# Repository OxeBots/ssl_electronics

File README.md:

# ssl_electronics
Oxebots electronics design for the RoboCup Soccer Small-Size League

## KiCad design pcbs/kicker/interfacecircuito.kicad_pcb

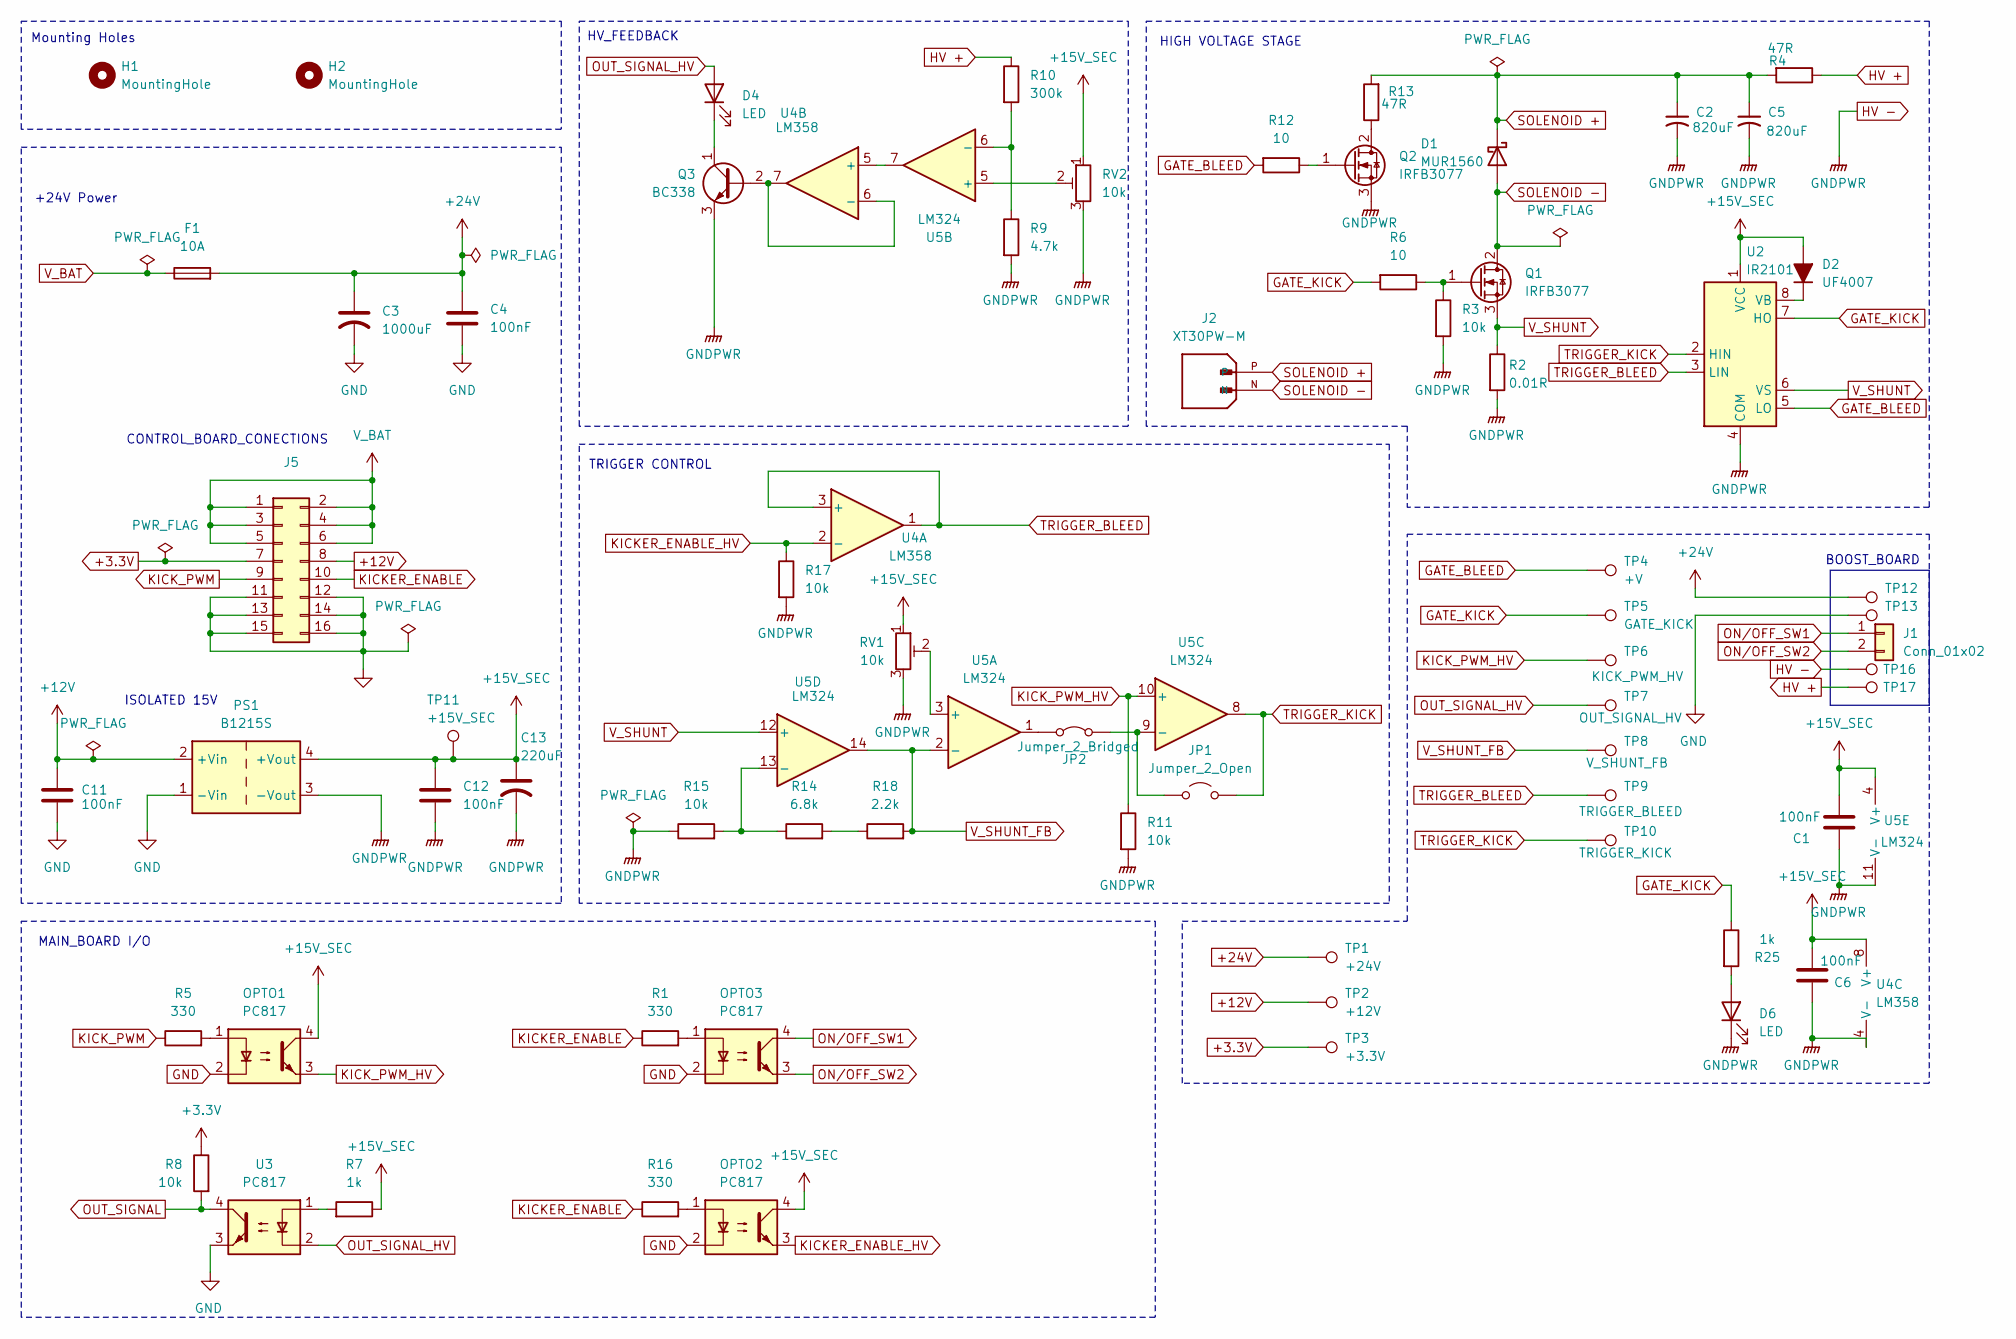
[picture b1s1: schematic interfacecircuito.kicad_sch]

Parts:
C1, C4, C6, C11, C12: 100nF; C_Disc_D5.0mm_W2.5mm_P2.50mm
C2, C5: 820uF; CP_Radial_D30.0mm_P10.00mm_SnapIn
C3: 1000uF; CP_Radial_D8.0mm_P5.00mm
C13: 220uF; CP_Radial_D8.0mm_P5.00mm
D1: MUR1560; TO-220-2_Vertical
D2: UF4007; D_DO-41_SOD81_P10.16mm_Horizontal
D4, D6: LED; LED_D5.0mm
F1: 10A; Fuse_Blade_ATO_directSolder
H1, H2: MountingHole; MountingHole_4.3mm_M4_Pad_Via
J1: Conn_01x02; JST_EH_B2B-EH-A_1x02_P2.50mm_Vertical
J2: XT30PW-M; AMASS_XT30PW-M; PARTREV 1.2
J5: Conn_02x08_Odd_Even; IDC-Header_2x08_P2.54mm_Vertical
JP1: Jumper_2_Open; SolderJumper-2_P1.3mm_Open_RoundedPad1.0x1.5mm
JP2: Jumper_2_Bridged; SolderJumper-2_P1.3mm_Bridged_RoundedPad1.0x1.5mm
OPTO1, OPTO2, OPTO3: PC817; DIP-4_W7.62mm
PS1: B1215S; DC-DC_Converter_BxxxxS_1W
Q1, Q2: IRFB3077; TO-220-3_Vertical
Q3: BC338; TO-92_Inline
R1, R5, R16: 330; R_Axial_DIN0207_L6.3mm_D2.5mm_P10.16mm_Horizontal
R2: 0.01R; R_Axial_DIN0516_L15.5mm_D5.0mm_P20.32mm_Horizontal
R3, R8, R11, R15, R17: 10k; R_Axial_DIN0207_L6.3mm_D2.5mm_P10.16mm_Horizontal
R4, R13: 47R; R_Axial_Power_L25.0mm_W9.0mm_P30.48mm
R6, R12: 10; R_Axial_DIN0207_L6.3mm_D2.5mm_P10.16mm_Horizontal
R7, R25: 1k; R_Axial_DIN0207_L6.3mm_D2.5mm_P10.16mm_Horizontal
R9: 4.7k; R_Axial_DIN0207_L6.3mm_D2.5mm_P10.16mm_Horizontal
R10: 300k; R_Axial_DIN0411_L9.9mm_D3.6mm_P15.24mm_Horizontal
R14: 6.8k; R_Axial_DIN0207_L6.3mm_D2.5mm_P10.16mm_Horizontal
R18: 2.2k; R_Axial_DIN0207_L6.3mm_D2.5mm_P10.16mm_Horizontal
RV1, RV2: 10k; Potentiometer_Bourns_3296W_Vertical
TP1: +24V; TestPoint_Pad_D1.5mm
TP2: +12V; TestPoint_Pad_D1.5mm
TP3: +3.3V; TestPoint_Pad_D1.5mm
TP4: +V; TestPoint_Pad_D1.5mm
TP5: GATE_KICK; TestPoint_Pad_D1.5mm
TP6: KICK_PWM_HV; TestPoint_Pad_D1.5mm
TP7: OUT_SIGNAL_HV; TestPoint_Pad_D1.5mm
TP8: V_SHUNT_FB; TestPoint_Pad_D1.5mm
TP9: TRIGGER_BLEED; TestPoint_Pad_D1.5mm
TP10: TRIGGER_KICK; TestPoint_Pad_D1.5mm
TP11: +15V_SEC; TestPoint_Pad_D1.5mm
TP12: V+; TestPoint_Plated_Hole_D2.0mm
TP13: GND; TestPoint_Plated_Hole_D2.0mm
TP16: HV-; TestPoint_Plated_Hole_D2.0mm
TP17: HV+; TestPoint_Plated_Hole_D2.0mm
U2: IR2101; SOIC-8_3.9x4.9mm_P1.27mm
U3: PC817; DIP-4_W7.62mm
U4: LM358; SOIC-8_3.9x4.9mm_P1.27mm
U5: LM324; SOIC-14_3.9x8.7mm_P1.27mm

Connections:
+3.3V: J5.7, R8.1, TP3.1 (1_1)
+12V: C11.1, J5.8, PS1.2 (+Vin), TP2.1 (1_1)
+15V_SEC: C1.1, C6.1, C12.1, C13.1, D2.2 (A), OPTO1.4, OPTO2.4, PS1.4 (+Vout), R7.1, RV1.1, RV2.1, TP11.1 (1_1), U2.1 (VCC), U4.8 (V+), U5.4 (V+)
+24V: C3.1, C4.1, F1.2, TP1.1 (1_1), TP12.1 (1_1)
GATE_BLEED: R12.2, TP4.1 (1_1), U2.5 (LO)
GATE_KICK: R6.2, R25.1, TP5.1 (1_1), U2.7 (HO)
GND: C3.2, C4.2, C11.2, J5.11, J5.12, J5.13, J5.14, J5.15, J5.16, OPTO1.2, OPTO2.2, OPTO3.2, PS1.1 (-Vin), TP13.1 (1_1), U3.3
HV +: R4.1, R10.1, TP17.1 (1_1)
HV -: C1.2, C2.2, C5.2, C6.2, C12.2, C13.2, D6.1 (K), PS1.3 (-Vout), Q2.3 (S), Q3.3 (E), R2.2, R3.2, R9.2, R11.2, R15.1, R17.2, RV1.3, RV2.3, TP16.1 (1_1), U2.4 (COM), U4.4 (V-), U5.11 (V-)
KICKER_ENABLE: J5.10, R1.1, R16.1
KICKER_ENABLE_HV: OPTO2.3, R17.1, U4.2 (-)
KICK_PWM: J5.9, R5.1
KICK_PWM_HV: OPTO1.3, R11.1, TP6.1 (1_1), U5.10 (+)
unnamed: D2.1 (K), U2.8 (VB)
unnamed: D4.1 (K), Q3.1 (C)
unnamed: D6.2 (A), R25.2
unnamed: JP1.1 (A), JP2.2 (B), U5.9 (-)
unnamed: JP2.1 (A), U5.1
unnamed: OPTO1.1, R5.2
unnamed: OPTO2.1, R16.2
unnamed: OPTO3.1, R1.2
unnamed: Q1.1 (G), R3.1, R6.1
unnamed: Q2.2 (D), R13.1
unnamed: Q2.1 (G), R12.1
unnamed: Q3.2 (B), U4.6 (-), U4.7
unnamed: R7.2, U3.1
unnamed: R14.2, R18.1
unnamed: U4.5 (+), U5.7
unnamed: RV1.2, U5.3 (+)
unnamed: RV2.2, U5.5 (+)
unnamed: R9.1, R10.2, U5.6 (-)
unnamed: R14.1, R15.2, U5.13 (-)
ON/OFF_SW1: J1.1, OPTO3.4
ON/OFF_SW2: J1.2, OPTO3.3
OUT_SIGNAL: R8.2, U3.4
OUT_SIGNAL_HV: D4.2 (A), TP7.1 (1_1), U3.2
SOLENOID +: C2.1, C5.1, D1.1 (K), J2.P, R4.2, R13.2
SOLENOID -: D1.2 (A), J2.N, Q1.2 (D)
TRIGGER_BLEED: TP9.1 (1_1), U2.3 (LIN), U4.1, U4.3 (+)
TRIGGER_KICK: JP1.2 (B), TP10.1 (1_1), U2.2 (HIN), U5.8
V_BAT: F1.1, J5.1, J5.2, J5.3, J5.4, J5.5, J5.6
V_SHUNT: Q1.3 (S), R2.1, U2.6 (VS), U5.12 (+)
V_SHUNT_FB: R18.2, TP8.1 (1_1), U5.2 (-), U5.14

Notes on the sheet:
CONTROL_BOARD_CONECTIONS
BOOST_BOARD
HIGH VOLTAGE STAGE
HV_FEEDBACK
TRIGGER CONTROL
MAIN_BOARD I/O
Mounting Holes
ISOLATED 15V
+24V Power

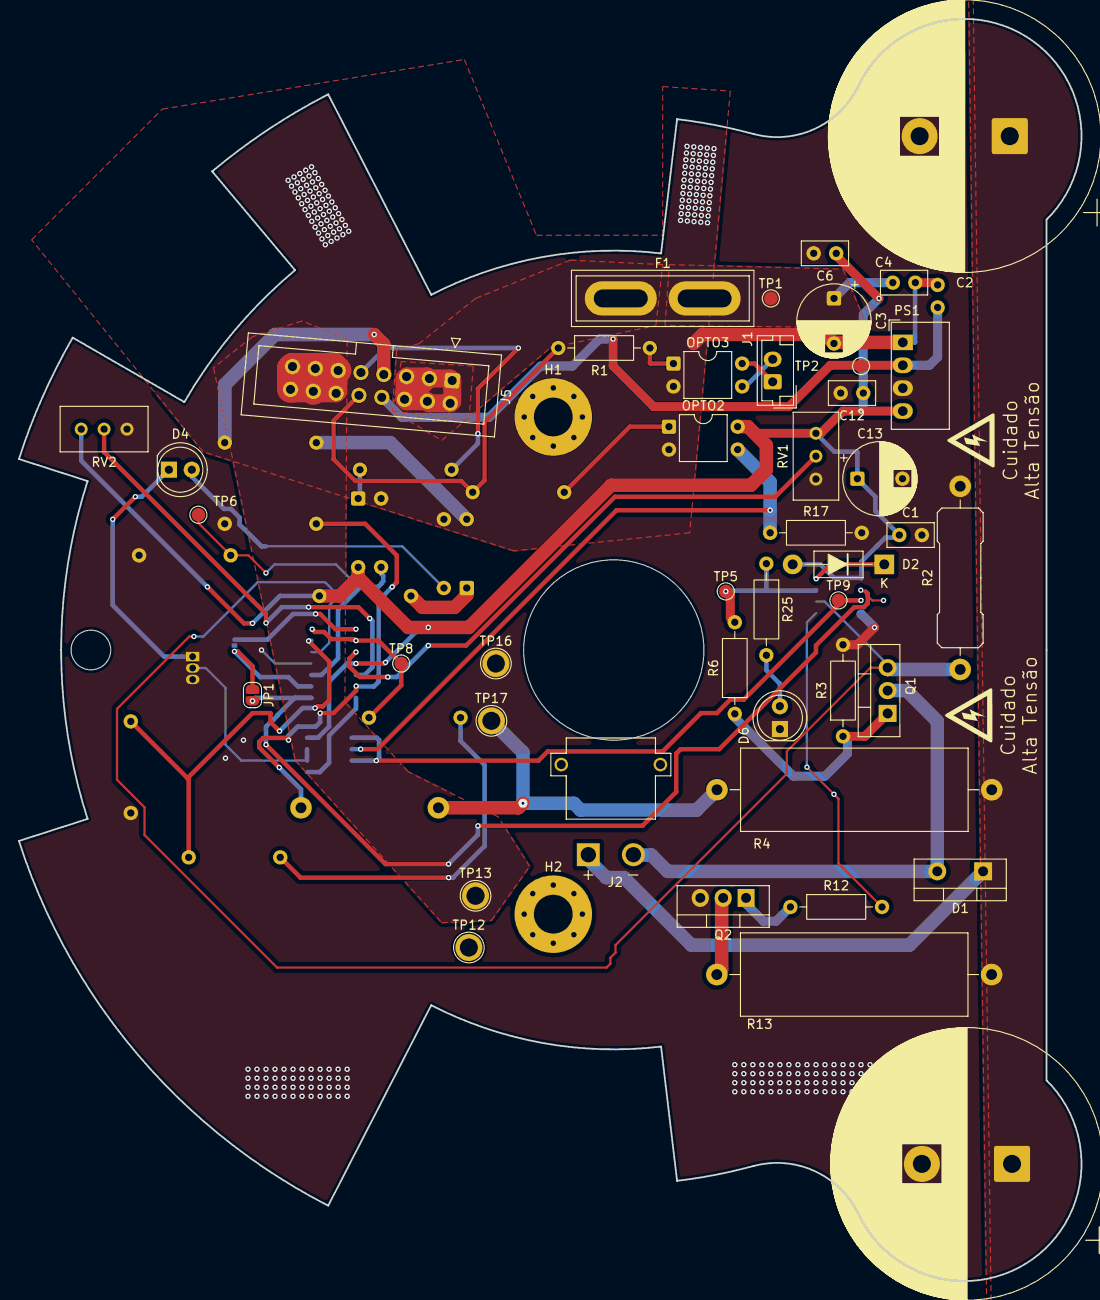
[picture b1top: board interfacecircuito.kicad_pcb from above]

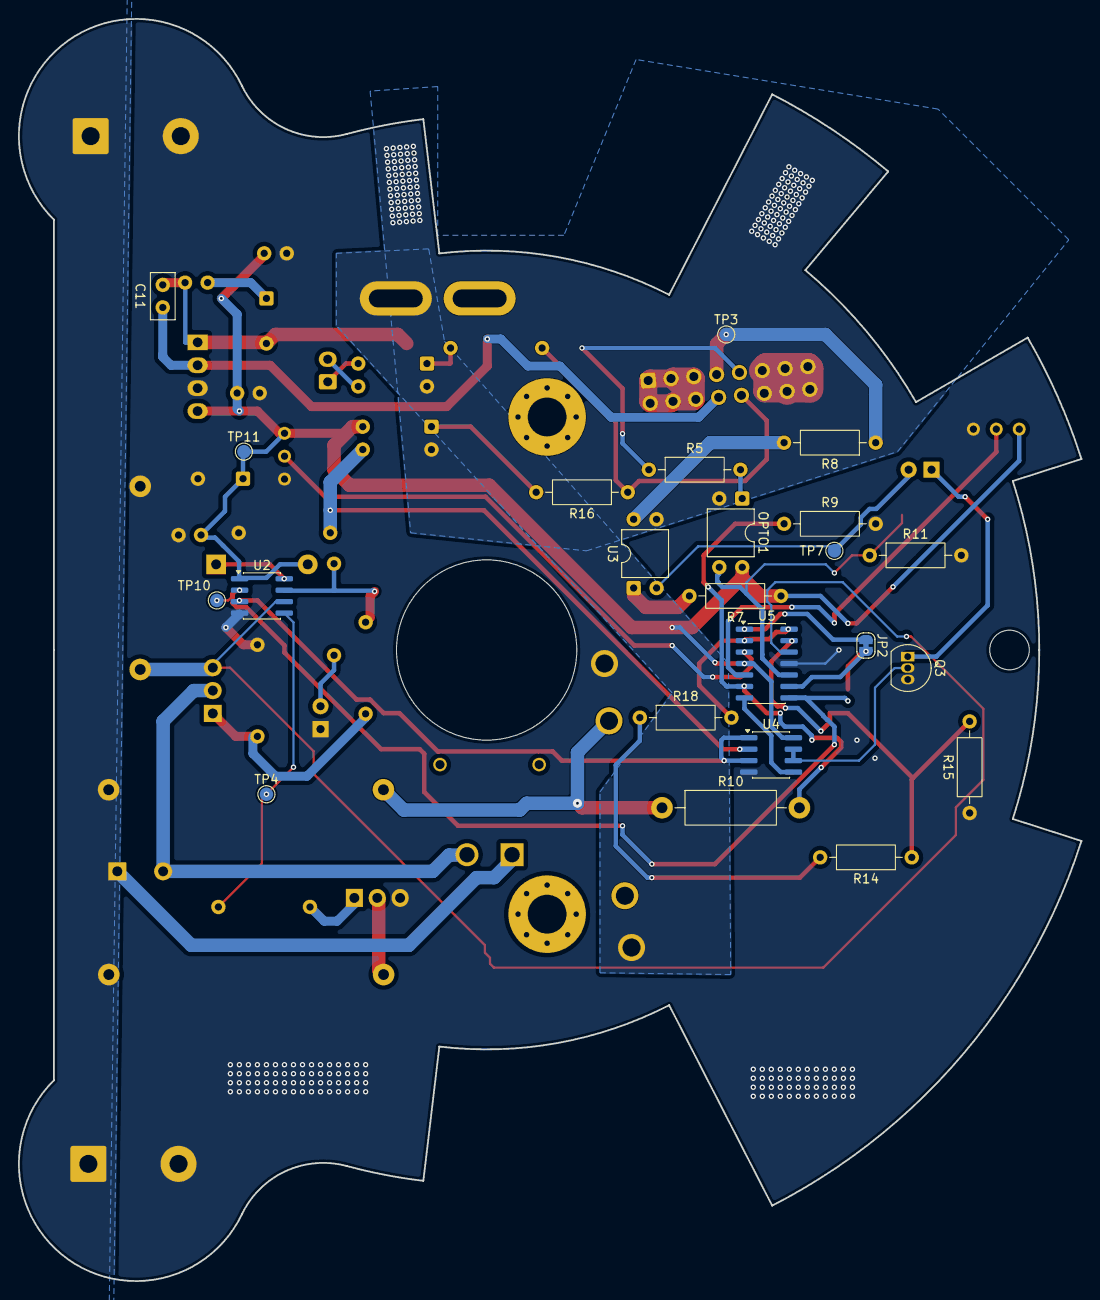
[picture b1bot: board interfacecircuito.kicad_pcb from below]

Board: 2 copper layers, 117.9 x 140.0 mm, 68 parts (23 on the bottom side), 43 nets.

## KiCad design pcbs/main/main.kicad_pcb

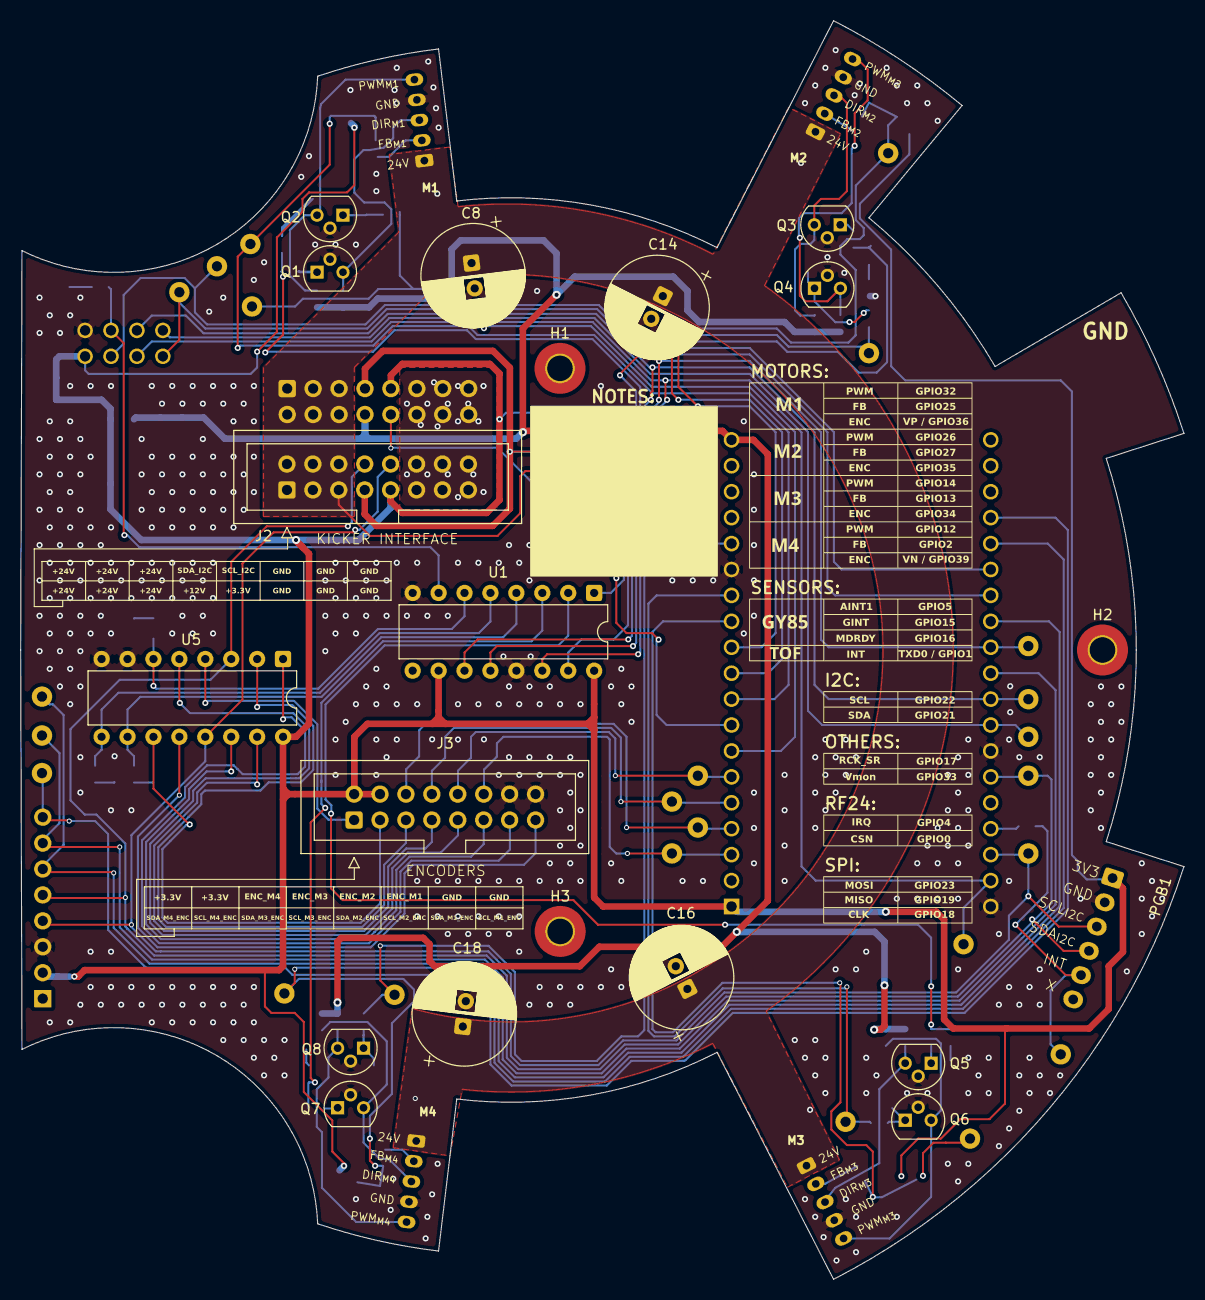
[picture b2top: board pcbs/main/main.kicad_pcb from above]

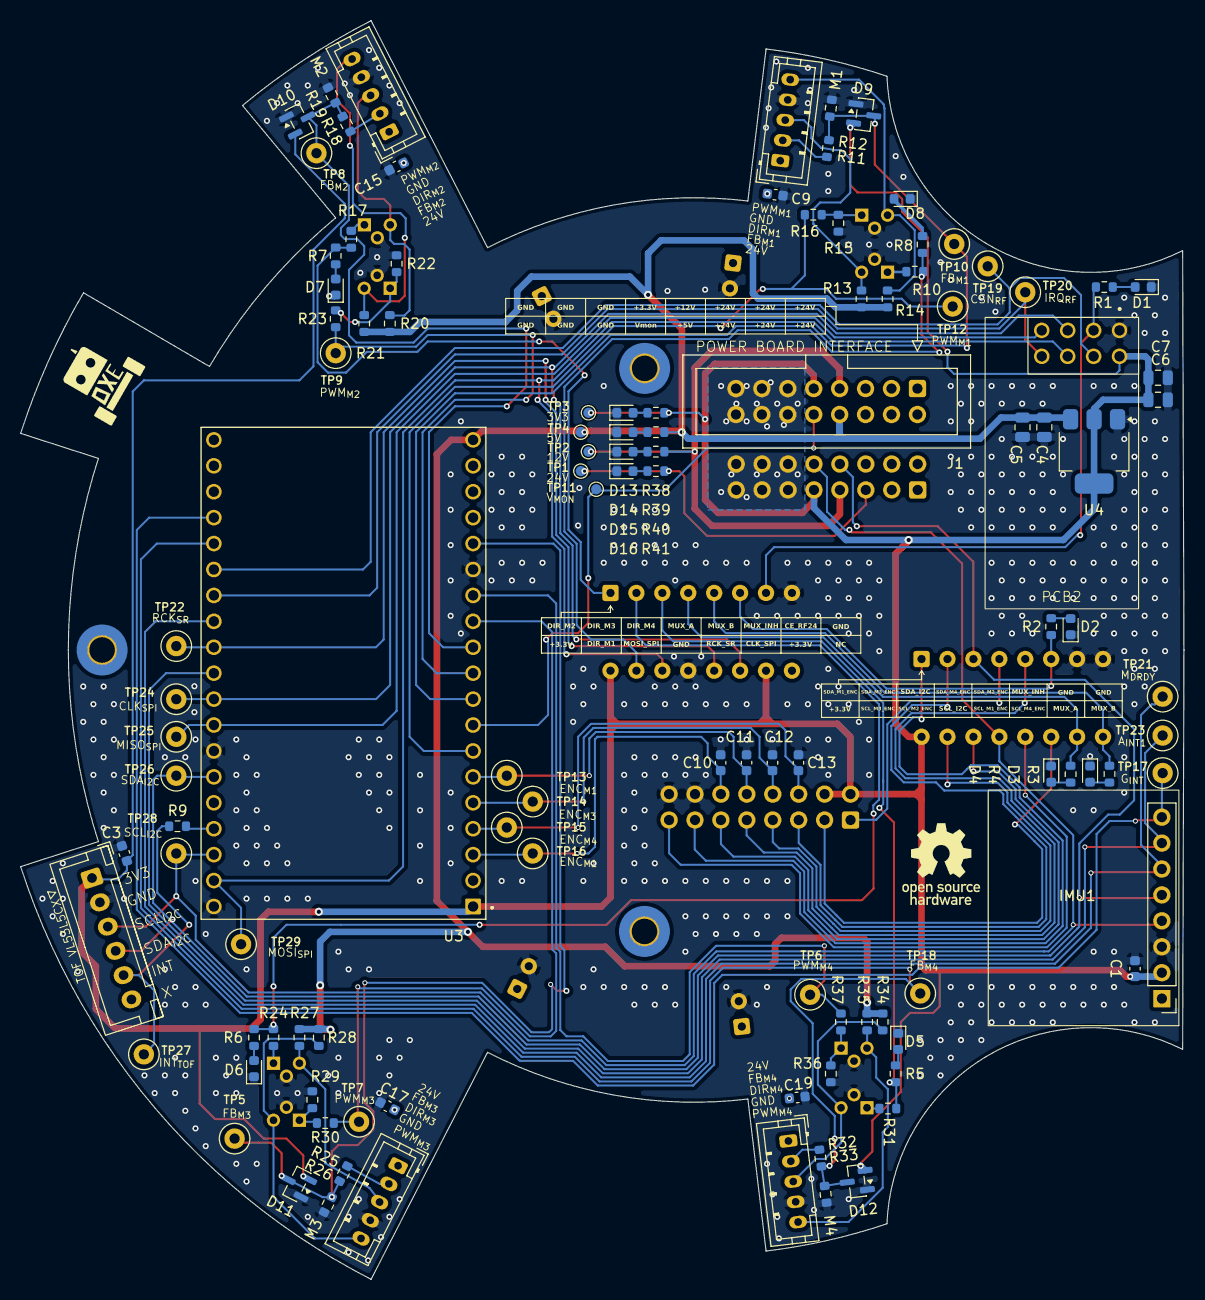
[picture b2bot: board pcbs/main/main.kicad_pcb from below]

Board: 2 copper layers, 114.0 x 123.3 mm, 129 parts (110 on the bottom side), 79 nets.

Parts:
C1, C3, C9, C10, C11, C12, C13, C15, C17, C19: 100 nF; C_0603_1608Metric
C4, C5, C6, C7: 10 uF; C_0805_2012Metric
C8, C14, C16, C18: 47uF; CP_Radial_D10.0mm_P2.50mm
D1, D2, D3, D4, D5, D6, D7, D8, D13, D14, D15, D16: LED; LED_0603_1608Metric
D9, D10, D11, D12: BAT54S; SOT-23
H1, H2, H3: MountingHole; MountingHole_2.5mm_Pad_TopBottom
IMU1: GY 85; GY-085
J1: PB_IDC_16_PIN; IDC-Header_2x08_P2.54mm_Vertical
J2: KICKER_IDC_16_PIN; IDC-Header_2x08_P2.54mm_Vertical
J3: ENC_IDC_16_PIN; IDC-Header_2x08_P2.54mm_Vertical
M1: FRONT_LEFT_MOTOR; HY-5_P2.00mm_Vertical
M2: BACK_LEFT_MOTOR; HY-5_P2.00mm_Vertical
M3: BACK_RIGHT_MOTOR; HY-5_P2.00mm_Vertical
M4: FRONT_RIGHT_MOTOR; HY-5_P2.00mm_Vertical
PCB1: VL53L5CX; JST_XH_B6B-XH-A_1x06_P2.50mm_Vertical
PCB2: NRF24L01
Q1, Q2, Q3, Q4, Q5, Q6, Q7, Q8: 2SC945; TO-92
R1, R2, R3, R4, R5, R6, R7, R8, R38, R39, R40, R41: 220; R_0603_1608Metric
R9, R10, R11, R13, R14, R16, R17, R18, R20, R21, R23, R24, R25, R27, R28, R30, R31, R32, R34, R35, R37: 10k; R_0603_1608Metric
R12, R19, R26, R33: 20k; R_0603_1608Metric
R15, R22, R29, R36: 47k; R_0603_1608Metric
TP1: 24V probe; TestPoint_Pad_D1.0mm
TP2: 12V probe; TestPoint_Pad_D1.0mm
TP3: 3.3V probe; TestPoint_Pad_D1.0mm
TP4: 5V probe; TestPoint_Pad_D1.0mm
TP5: M3_FB_Probe; TestPoint_Loop_D2.50mm_Drill1.0mm_LowProfile
TP6: M4_PWM_Probe; TestPoint_Loop_D2.50mm_Drill1.0mm_LowProfile
TP7: M3_PWM_Probe; TestPoint_Loop_D2.50mm_Drill1.0mm_LowProfile
TP8: M2_FB_Probe; TestPoint_Loop_D2.50mm_Drill1.0mm_LowProfile
TP9: M2_PWM_Probe; TestPoint_Loop_D2.50mm_Drill1.0mm_LowProfile
TP10: M1_FB_Probe; TestPoint_Loop_D2.50mm_Drill1.0mm_LowProfile
TP11: V_{mon} probe; TestPoint_Pad_D1.0mm
TP12: M1_PWM_Probe; TestPoint_Loop_D2.50mm_Drill1.0mm_LowProfile
TP13: M2_{ENC} probe; TestPoint_Loop_D2.50mm_Drill1.0mm_LowProfile
TP14: M3_{ENC} probe; TestPoint_Loop_D2.50mm_Drill1.0mm_LowProfile
TP15: M4_{ENC} probe; TestPoint_Loop_D2.50mm_Drill1.0mm_LowProfile
TP16: M1_{ENC} probe; TestPoint_Loop_D2.50mm_Drill1.0mm_LowProfile
TP17: G_{INT} probe; TestPoint_Loop_D2.50mm_Drill1.0mm_LowProfile
TP18: M4_FB_Probe; TestPoint_Loop_D2.50mm_Drill1.0mm_LowProfile
TP19: CSN_{RF24} probe; TestPoint_Loop_D2.50mm_Drill1.0mm_LowProfile
TP20: IRQ_{RF24} probe; TestPoint_Loop_D2.50mm_Drill1.0mm_LowProfile
TP21: M_{RDY} probe; TestPoint_Loop_D2.50mm_Drill1.0mm_LowProfile
TP22: SR_LATCH probe; TestPoint_Loop_D2.50mm_Drill1.0mm_LowProfile
TP23: A_{INT1} probe; TestPoint_Loop_D2.50mm_Drill1.0mm_LowProfile
TP24: CLK_{SPI} probe; TestPoint_Loop_D2.50mm_Drill1.0mm_LowProfile
TP25: MISO_{SPI} probe; TestPoint_Loop_D2.50mm_Drill1.0mm_LowProfile
TP26: SDA_{I2C}; TestPoint_Loop_D2.50mm_Drill1.0mm_LowProfile
TP27: INT_{TOF}; TestPoint_Loop_D2.50mm_Drill1.0mm_LowProfile
TP28: SCL_{I2C}; TestPoint_Loop_D2.50mm_Drill1.0mm_LowProfile
TP29: MOSI_{SPI} probe; TestPoint_Loop_D2.50mm_Drill1.0mm_LowProfile
U1: 74HC595; DIP-16_W7.62mm
U3: ESP32-DEVKITC-32U; MODULE_ESP32-DEVKITC-32U
U4: AMS1117-3.3; SOT-223-3_TabPin2
U5: 4052; DIP-16_W7.62mm

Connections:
+3.3V: C1.2, C3.2, C6.2, C7.2, D9.2 (K), D10.2 (K), D11.2 (K), D12.2 (K), IMU1.2, J1.9, J2.9, J3.2, J3.4, PCB1.1 (VIN), PCB2.5 (VCC), R38.1, TP3.1 (1_1), U1.10 (~SRCLR), U1.16 (VCC), U3.1 (3V3), U4.2 (VO), U5.16 (VDD)
+5V: C4.2, C5.2, J1.8, R13.2, R14.2, R20.2, R21.2, R27.2, R28.2, R34.2, R35.2, R39.1, TP4.1 (1_1), U3.19 (EXT_5V), U4.3 (VI)
+12V: J1.7, J2.7, R40.1, TP2.1 (1_1)
+24V: C8.1, C9.1, C14.1, C15.1, C16.1, C17.1, C18.1, C19.1, J1.1, J1.2, J1.3, J1.4, J1.5, J1.6, J2.1, J2.2, J2.3, J2.4, J2.5, J2.6, M1.1 (VCC), M2.1 (VCC), M3.1 (VCC), M4.1 (VCC), R41.1, TP1.1 (1_1)
/motors/SCL_{M1_ENC}: J3.15, U5.12 (X0)
/motors/SCL_{M2_ENC}: J3.11, U5.14 (X1)
/motors/SCL_{M3_ENC}: J3.7, U5.15 (X2)
/motors/SCL_{M4_ENC}: J3.3, U5.11 (X3)
/motors/SDA_{M1_ENC}: J3.13, U5.1 (Y0)
/motors/SDA_{M2_ENC}: J3.9, U5.5 (Y1)
/motors/SDA_{M3_ENC}: J3.5, U5.2 (Y2)
/motors/SDA_{M4_ENC}: J3.1, U5.4 (Y3)
A_{INT1}: IMU1.7, TP23.1 (1_1), U3.29 (IO5)
CE_{RF24}: PCB2.2 (CE), R1.1, U1.7 (QH)
CLK_{SPI}: PCB2.3 (SCK), TP24.1 (1_1), U1.11 (SRCLK), U3.30 (IO18)
CSN_{RF24}: PCB2.6 (CSN), TP19.1 (1_1), U3.25 (IO0)
DIR_{M1}: R8.1, R10.1, U1.15 (QA)
DIR_{M2}: R7.1, R17.1, U1.1 (QB)
DIR_{M3}: R6.1, R24.1, U1.2 (QC)
DIR_{M4}: R5.1, R31.1, U1.3 (QD)
ENC_{M1}: C10.1, J3.12, TP16.1 (1_1), U3.3 (SENSOR_VP)
ENC_{M2}: C11.1, J3.10, TP13.1 (1_1), U3.6 (IO35)
ENC_{M3}: C12.1, J3.8, TP14.1 (1_1), U3.5 (IO34)
ENC_{M4}: C13.1, J3.6, TP15.1 (1_1), U3.4 (SENSOR_VN)
FB_{M1}: D9.3 (COM), R11.1, R12.2, TP10.1 (1_1), U3.9 (IO25)
FB_{M2}: D10.3 (COM), R18.1, R19.2, TP8.1 (1_1), U3.11 (IO27)
FB_{M3}: D11.3 (COM), R25.1, R26.2, TP5.1 (1_1), U3.15 (IO13)
FB_{M4}: D12.3 (COM), R32.1, R33.2, TP18.1 (1_1), U3.24 (IO2)
GND: C1.1, C3.1, C4.1, C5.1, C6.1, C7.1, C8.2, C9.2, C10.2, C11.2, C12.2, C13.2, C14.2, C15.2, C16.2, C17.2, C18.2, C19.2, D1.1 (K), D2.1 (K), D3.1 (K), D4.1 (K), D5.1 (K), D6.1 (K), D7.1 (K), D8.1 (K), D9.1 (A), D10.1 (A), D11.1 (A), D12.1 (A), D13.1 (K), D14.1 (K), D15.1 (K), D16.1 (K), IMU1.3, J1.11, J1.12, J1.13, J1.14, J1.15, J1.16, J2.11, J2.12, J2.13, J2.14, J2.15, J2.16, J3.14, J3.16, M1.4 (GND), M2.4 (GND), M3.4 (GND), M4.4 (GND), PCB1.2 (GND), PCB2.1 (GND), Q1.2 (E), Q2.2 (E), Q3.2 (E), Q4.2 (E), Q5.2 (E), Q6.2 (E), Q7.2 (E), Q8.2 (E), R12.1, R15.2, R19.1, R22.2, R26.1, R29.2, R33.1, R36.2, U1.8 (GND), U1.13 (~OE), U3.14 (GND1), U3.32 (GND2), U3.38 (GND3), U4.1 (GND), U5.7 (VEE), U5.8 (VSS)
G_{INT}: IMU1.8, TP17.1 (1_1), U3.23 (IO15)
INT_{TOF}: PCB1.5 (INT), R9.1, TP27.1 (1_1)
IRQ_{RF24}: PCB2.8 (IRQ), TP20.1 (1_1), U3.26 (IO4)
MISO_{SPI}: PCB2.4 (MISO), TP25.1 (1_1), U3.31 (IO19)
MOSI_{SPI}: PCB2.7 (MOSI), TP29.1 (1_1), U1.14 (SER), U3.37 (IO23)
MUX_{A}: R4.1, U1.4 (QE), U5.10 (A)
MUX_{B}: R3.1, U1.5 (QF), U5.9 (B)
MUX_{INH}: R2.1, U1.6 (QG), U5.6 (Inh)
M_{DRDY}: IMU1.6, TP21.1 (1_1), U3.27 (IO16)
unnamed: D1.2 (A), R1.2
unnamed: D2.2 (A), R2.2
unnamed: D3.2 (A), R3.2
unnamed: D4.2 (A), R4.2
unnamed: D5.2 (A), R5.2
unnamed: D6.2 (A), R6.2
unnamed: D7.2 (A), R7.2
unnamed: D8.2 (A), R8.2
unnamed: D13.2 (A), R38.2
unnamed: D14.2 (A), R39.2
unnamed: D15.2 (A), R40.2
unnamed: D16.2 (A), R41.2
unnamed: M1.3 (DIR), Q1.3 (C), R13.1
unnamed: M1.2 (Feedback), R11.2
unnamed: M1.5 (PWM), Q2.3 (C), R14.1
unnamed: M2.3 (DIR), Q3.3 (C), R20.1
unnamed: M2.2 (Feedback), R18.2
unnamed: M2.5 (PWM), Q4.3 (C), R21.1
unnamed: M3.3 (DIR), Q5.3 (C), R27.1
unnamed: M3.2 (Feedback), R25.2
unnamed: M3.5 (PWM), Q6.3 (C), R28.1
unnamed: M4.3 (DIR), Q7.3 (C), R34.1
unnamed: M4.2 (Feedback), R32.2
unnamed: M4.5 (PWM), Q8.3 (C), R35.1
unnamed: Q1.1 (B), R10.2
unnamed: Q2.1 (B), R15.1, R16.2
unnamed: Q3.1 (B), R17.2
unnamed: Q4.1 (B), R22.1, R23.2
unnamed: Q5.1 (B), R24.2
unnamed: Q6.1 (B), R29.1, R30.2
unnamed: Q7.1 (B), R31.2
unnamed: Q8.1 (B), R36.1, R37.2
unnamed: R9.2, U3.35 (TXD0)
PWM_{M1}: R16.1, TP12.1 (1_1), U3.7 (IO32)
PWM_{M2}: R23.1, TP9.1 (1_1), U3.10 (IO26)
PWM_{M3}: R30.1, TP7.1 (1_1), U3.12 (IO14)
PWM_{M4}: R37.1, TP6.1 (1_1), U3.13 (IO12)
RCK_{SR}: TP22.1 (1_1), U1.12 (RCLK), U3.28 (IO17)
SCL_{I2C}: IMU1.4, J2.10, PCB1.3 (SCL_{I2C}), TP28.1 (1_1), U3.36 (IO22), U5.13 (X)
SDA_{I2C}: IMU1.5, J2.8, PCB1.4 (SDA_{I2C}), TP26.1 (1_1), U3.33 (IO21), U5.3 (Y)
V_{mon}: J1.10, TP11.1 (1_1), U3.8 (IO33)

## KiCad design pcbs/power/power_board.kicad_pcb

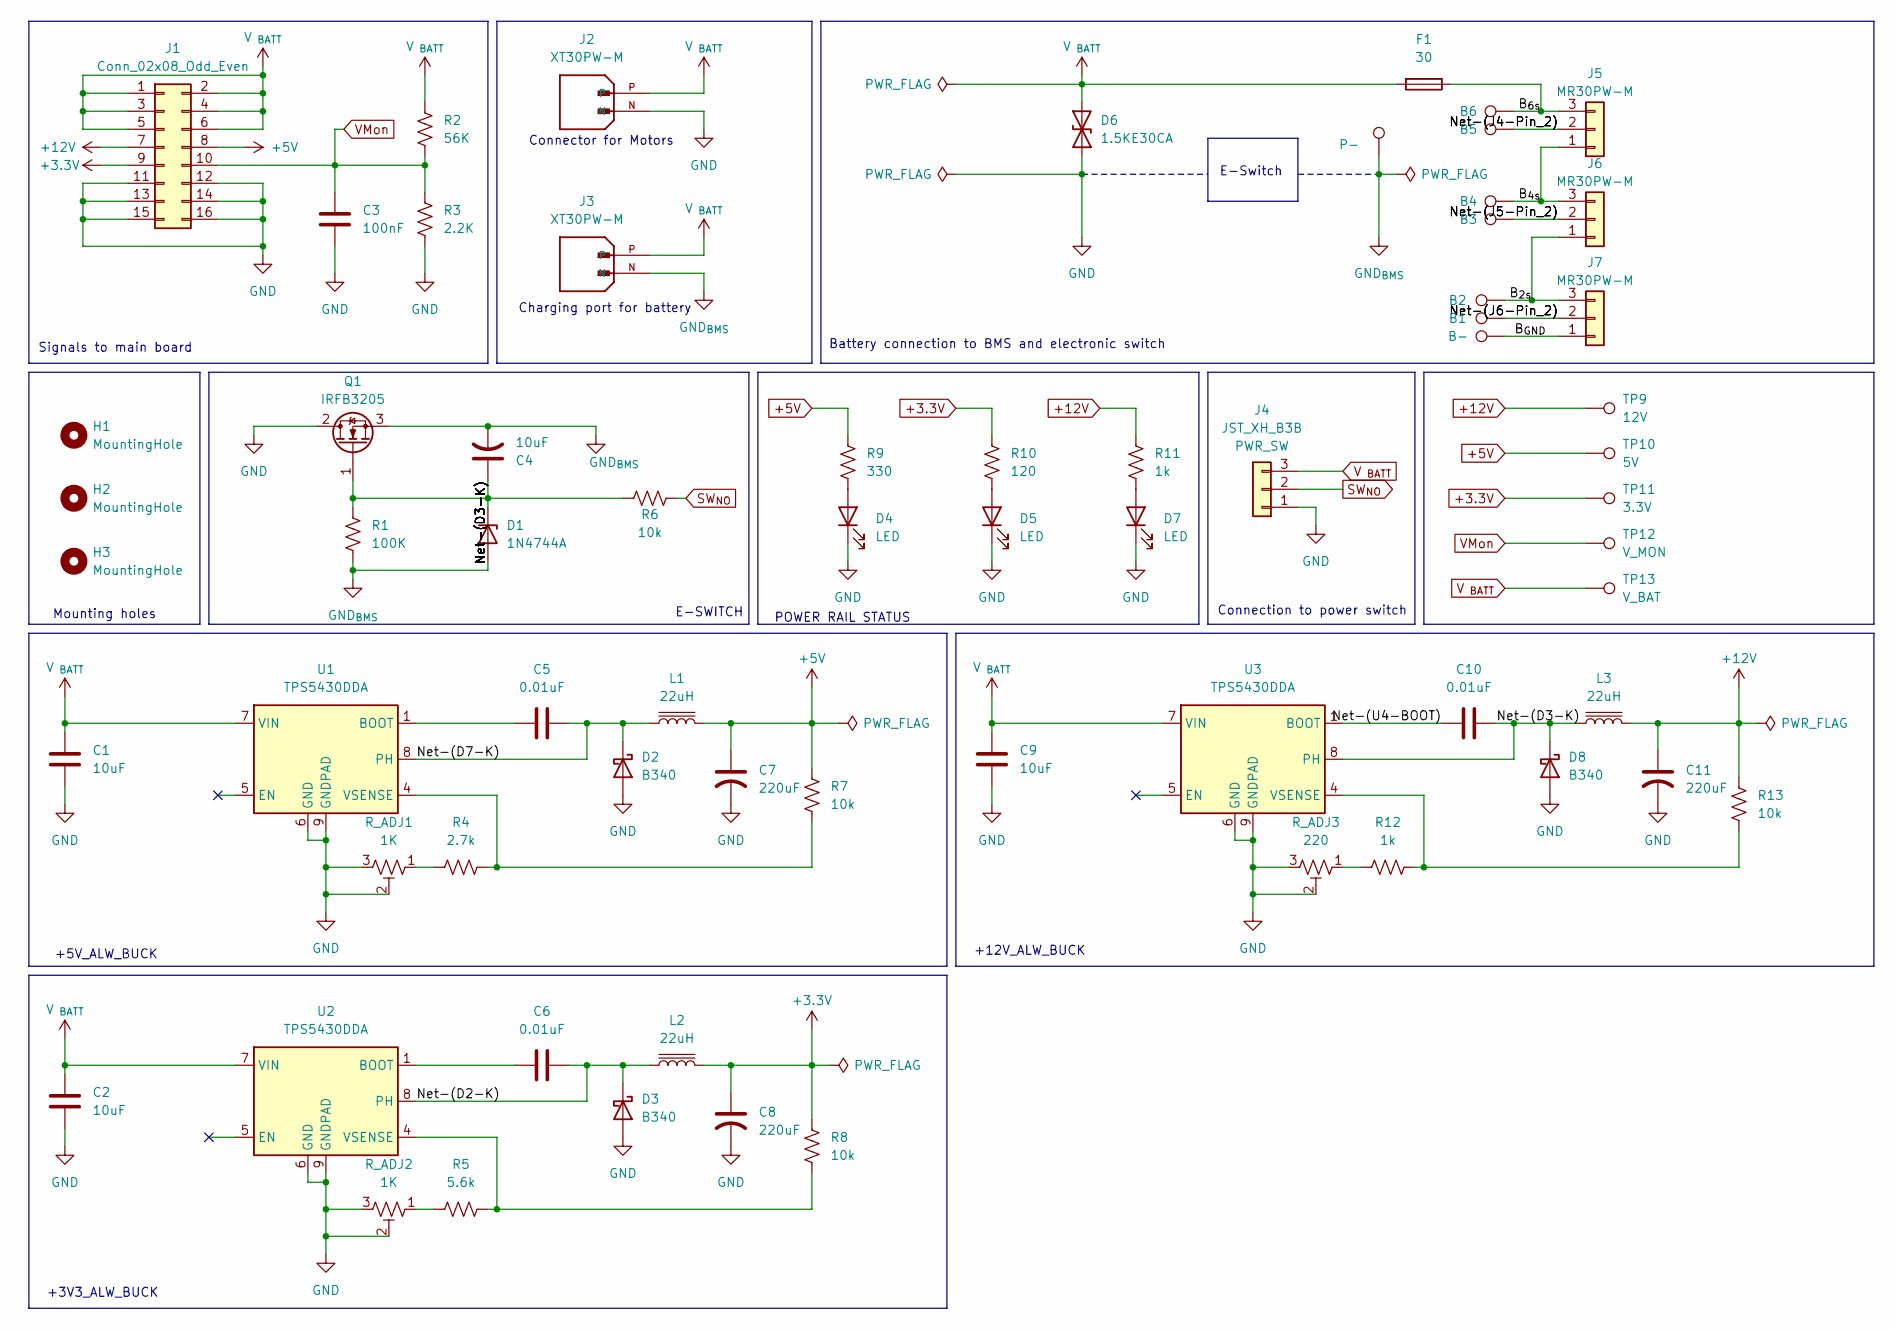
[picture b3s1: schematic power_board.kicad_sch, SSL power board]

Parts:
C1, C2, C4, C9: 10uF; CP_Radial_D5.0mm_P2.50mm
C3: 100nF; C_Disc_D3.0mm_W1.6mm_P2.50mm
C5, C6, C10: 0.01uF; C_Disc_D3.0mm_W1.6mm_P2.50mm
C7, C8: 220uF; CP_Elec_6.3x7.7
C11: 220uF; CP_Elec_8x6.2
D1: 1N4744A; D_DO-41_SOD81_P10.16mm_Horizontal
D2, D3, D8: B340; D_SMC
D4, D5, D7: LED; LED_0805_2012Metric
D6: 1.5KE30CA; D_DO-201AE_P15.24mm_Horizontal
F1: 30; Fuseholder_Blade_Mini_Keystone_3568
H1, H2, H3: MountingHole; MountingHole_3.2mm_M3
J1: Conn_02x08_Odd_Even; IDC-Header_2x08_P2.54mm_Vertical
J2, J3: XT30PW-M; AMASS_XT30PW-M; PARTREV 1.2
J4: JST_XH_B3B; JST_XH_B3B-XH-A_1x03_P2.50mm_Vertical
J5, J6, J7: MR30PW-M; AMASS_MR30PW-M_1x03_P3.50mm_Horizontal
L1, L2, L3: 22uH; L_6.3x6.3_H3
Q1: IRFB3205; TO-220-3_Vertical
R1: 100K; R_Axial_DIN0204_L3.6mm_D1.6mm_P5.08mm_Horizontal
R2: 56K; R_Axial_DIN0204_L3.6mm_D1.6mm_P5.08mm_Horizontal
R3: 2.2K; R_Axial_DIN0204_L3.6mm_D1.6mm_P5.08mm_Horizontal
R4: 2.7k; R_0805_2012Metric
R5: 5.6k; R_0805_2012Metric
R6: 10k; R_Axial_DIN0204_L3.6mm_D1.6mm_P5.08mm_Horizontal
R7, R8, R13: 10k; R_0805_2012Metric
R9: 330; R_0805_2012Metric
R10: 120; R_0805_2012Metric
R11, R12: 1k; R_0805_2012Metric
R_ADJ1, R_ADJ2: 1K; Potentiometer_Bourns_3314G_Vertical
R_ADJ3: 220; Potentiometer_Bourns_3314G_Vertical
TP2: B2; TestPoint_THTPad_D2.0mm_Drill1.0mm
TP3: B1; TestPoint_THTPad_D2.0mm_Drill1.0mm
TP4: B-; SolderWirePad_1x01_SMD_5x10mm
TP5: B6; TestPoint_THTPad_D2.0mm_Drill1.0mm
TP6: B5; TestPoint_THTPad_D2.0mm_Drill1.0mm
TP7: B4; TestPoint_THTPad_D2.0mm_Drill1.0mm
TP8: B3; TestPoint_THTPad_D2.0mm_Drill1.0mm
TP9: 12V; TestPoint_THTPad_D2.0mm_Drill1.0mm
TP10: 5V; TestPoint_THTPad_D2.0mm_Drill1.0mm
TP11: 3.3V; TestPoint_THTPad_D2.0mm_Drill1.0mm
TP12: V_MON; TestPoint_THTPad_D2.0mm_Drill1.0mm
TP13: V_BAT; TestPoint_THTPad_D2.0mm_Drill1.0mm
TP15: P-; SolderWirePad_1x01_SMD_5x10mm
U1, U2, U3: TPS5430DDA; TI_SO-PowerPAD-8_ThermalVias

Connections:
+3.3V: C8.1, J1.9, L2.2, R8.1, R10.1, TP11.1 (1_1)
+5V: C7.1, J1.8, L1.2, R7.1, R9.1, TP10.1 (1_1)
+12V: C11.1, J1.7, L3.2, R11.1, R13.1, TP9.1 (1_1)
/B_{2s}: J6.1, J7.3, TP2.1 (1_1)
/B_{4s}: J5.1, J6.3, TP7.1 (1_1)
/B_{6s}: F1.1, J5.3, TP5.1 (1_1)
/B_{GND}: J7.1, TP4.1 (1_1)
/Net-(D2-K): C6.2, D3.1 (K), L2.1, U2.8 (PH)
/Net-(D7-K): C5.2, D2.1 (K), L1.1, U1.8 (PH)
/Net-(J4-Pin_2): J5.2, TP6.1 (1_1)
/Net-(J5-Pin_2): J6.2, TP8.1 (1_1)
/Net-(J6-Pin_2): J7.2, TP3.1 (1_1)
/Net-(U4-BOOT): C10.1, U3.1 (BOOT)
GND: C1.2, C2.2, C3.2, C7.2, C8.2, C9.2, C11.2, D2.2 (A), D3.2 (A), D4.1 (K), D5.1 (K), D6.2 (A2), D7.1 (K), D8.2 (A), J1.11, J1.12, J1.13, J1.14, J1.15, J1.16, J2.N, J4.1, Q1.2 (D), R3.2, R_ADJ1.2, R_ADJ1.3, R_ADJ2.2, R_ADJ2.3, R_ADJ3.2, R_ADJ3.3, U1.6 (GND), U1.9 (GNDPAD), U2.6 (GND), U2.9 (GNDPAD), U3.6 (GND), U3.9 (GNDPAD)
GND_{BMS}: C4.2, D1.2 (A), J3.N, Q1.3 (S), R1.2, TP15.1 (1_1)
unnamed: D4.2 (A), R9.2
unnamed: D5.2 (A), R10.2
unnamed: D7.2 (A), R11.2
unnamed: R4.1, R_ADJ1.1
unnamed: R5.1, R_ADJ2.1
unnamed: R12.1, R_ADJ3.1
unnamed: C5.1, U1.1 (BOOT)
unnamed: R4.2, R7.2, U1.4 (VSENSE)
unnamed: C6.1, U2.1 (BOOT)
unnamed: R5.2, R8.2, U2.4 (VSENSE)
unnamed: R12.2, R13.2, U3.4 (VSENSE)
SW_{NO}: J4.2, R6.1
VMon: C3.1, J1.10, R2.2, R3.1, TP12.1 (1_1)
V_{ BATT}: C1.1, C2.1, C9.1, D6.1 (A1), F1.2, J1.1, J1.2, J1.3, J1.4, J1.5, J1.6, J2.P, J3.P, J4.3, R2.1, TP13.1 (1_1), U1.7 (VIN), U2.7 (VIN), U3.7 (VIN)

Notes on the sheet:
Signals to main board
E-Switch
POWER RAIL STATUS
Charging port for battery
Connector for Motors
Battery connection to BMS and electronic switch
Mounting holes
Connection to power switch
E-SWITCH
+12V_ALW_BUCK
+5V_ALW_BUCK
+3V3_ALW_BUCK

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

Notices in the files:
main/pcbs/main/main.kicad_pcb:
https://creativecommons.org/licenses/by/4.0
License: CC BY 4.0
